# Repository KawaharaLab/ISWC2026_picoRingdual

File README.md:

# picoRing *dual*

This repository contains the hardware design files, firmware, and evaluation applications for the dual-wearable system (Finger Ring and Wristband) presented in our ISWC 2026 paper.

---

## Repository Structure

The project consists of four main modules:

### 1. BLE (`/BLE`)
Contains the firmware used for baseline evaluation.
* **`ring_demo/` / `receiver_demo/`**: Firmware implemented to benchmark power consumption when the ring and wristband communicate via Bluetooth Low Energy (BLE) instead of NFC.

### 2. Circuit (`/Circuit`)
Contains the hardware design files created with KiCad (v7 or later).
* **`ring/`**: Schematic and PCB layout files for the finger-worn ring node.
* **`wristband/`**: Schematic and PCB layout files for the wristband module.

### 3. Firmware (`/Firmware`)
Contains the source code for the proposed NFC-coupled system.
* **`ring/`**: STM32CubeIDE project for the STM32U375KGUx MCU embedded in the ring, including drivers for the `ICM45605` IMU and `ST25DVxxKC` NFC tag.
* **`wristband/`**: PlatformIO project for the Seeed Studio XIAO based wristband, utilizing the ST `NFC-RFAL` library for NFC polling.

### 4. GUI (`/GUI`)
Contains the following applications for system demonstration and data visualization:
* **`sensor_viewer/`**: Displays raw data from the trackball and IMU quaternion outputs.
* **`3d_viewer/`**: Visualizes data from both hands' trackballs and IMU sensors to dynamically control 3D models of the ring and trackball icons.
* **`map/`**: A web-based application that displays routes selected from a menu. Supports map scrolling and zooming via the trackball (Requires a Google Maps API key).
* **`game/`**: A 3D application with two selectable modes via a menu:
  * **Video Mode**: Supports playback, pausing, and skipping of videos.
  * **Game Mode**: Enables aiming and reloading with the right hand, and locomotion with the left hand.
* **`email/`**: Supports email selection and message body scrolling.
* **`cooking/`**: Detects hand movements via the IMU and triggers a warning alert if the hand stops moving for a specific duration.

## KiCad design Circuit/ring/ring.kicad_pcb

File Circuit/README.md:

# Hardware Circuit Design

This directory contains the hardware design and PCB layout files for the *picoRing dual* system. 

## Directory Structure

* **`ring/`**: Schematic and PCB design files for the  ring.
* **`wristband/`**: Schematic and PCB design files for the wristband.

---

## Design Environment

* **Software**: **KiCad (v7.0 or later)**
* **Project Files**: `.kicad_pro`

To inspect or modify the designs, open the respective `.kicad_pro` file inside the `ring/` or `wristband/` directory using KiCad.

---

## Important Notice for Replication

* **Component Footprints & Libraries**: Custom or third-party footprint/symbol libraries used in these designs are not bundled in this repository. Users must set up, map, or substitute their own component libraries and footprints according to their local KiCad environment and parts availability.

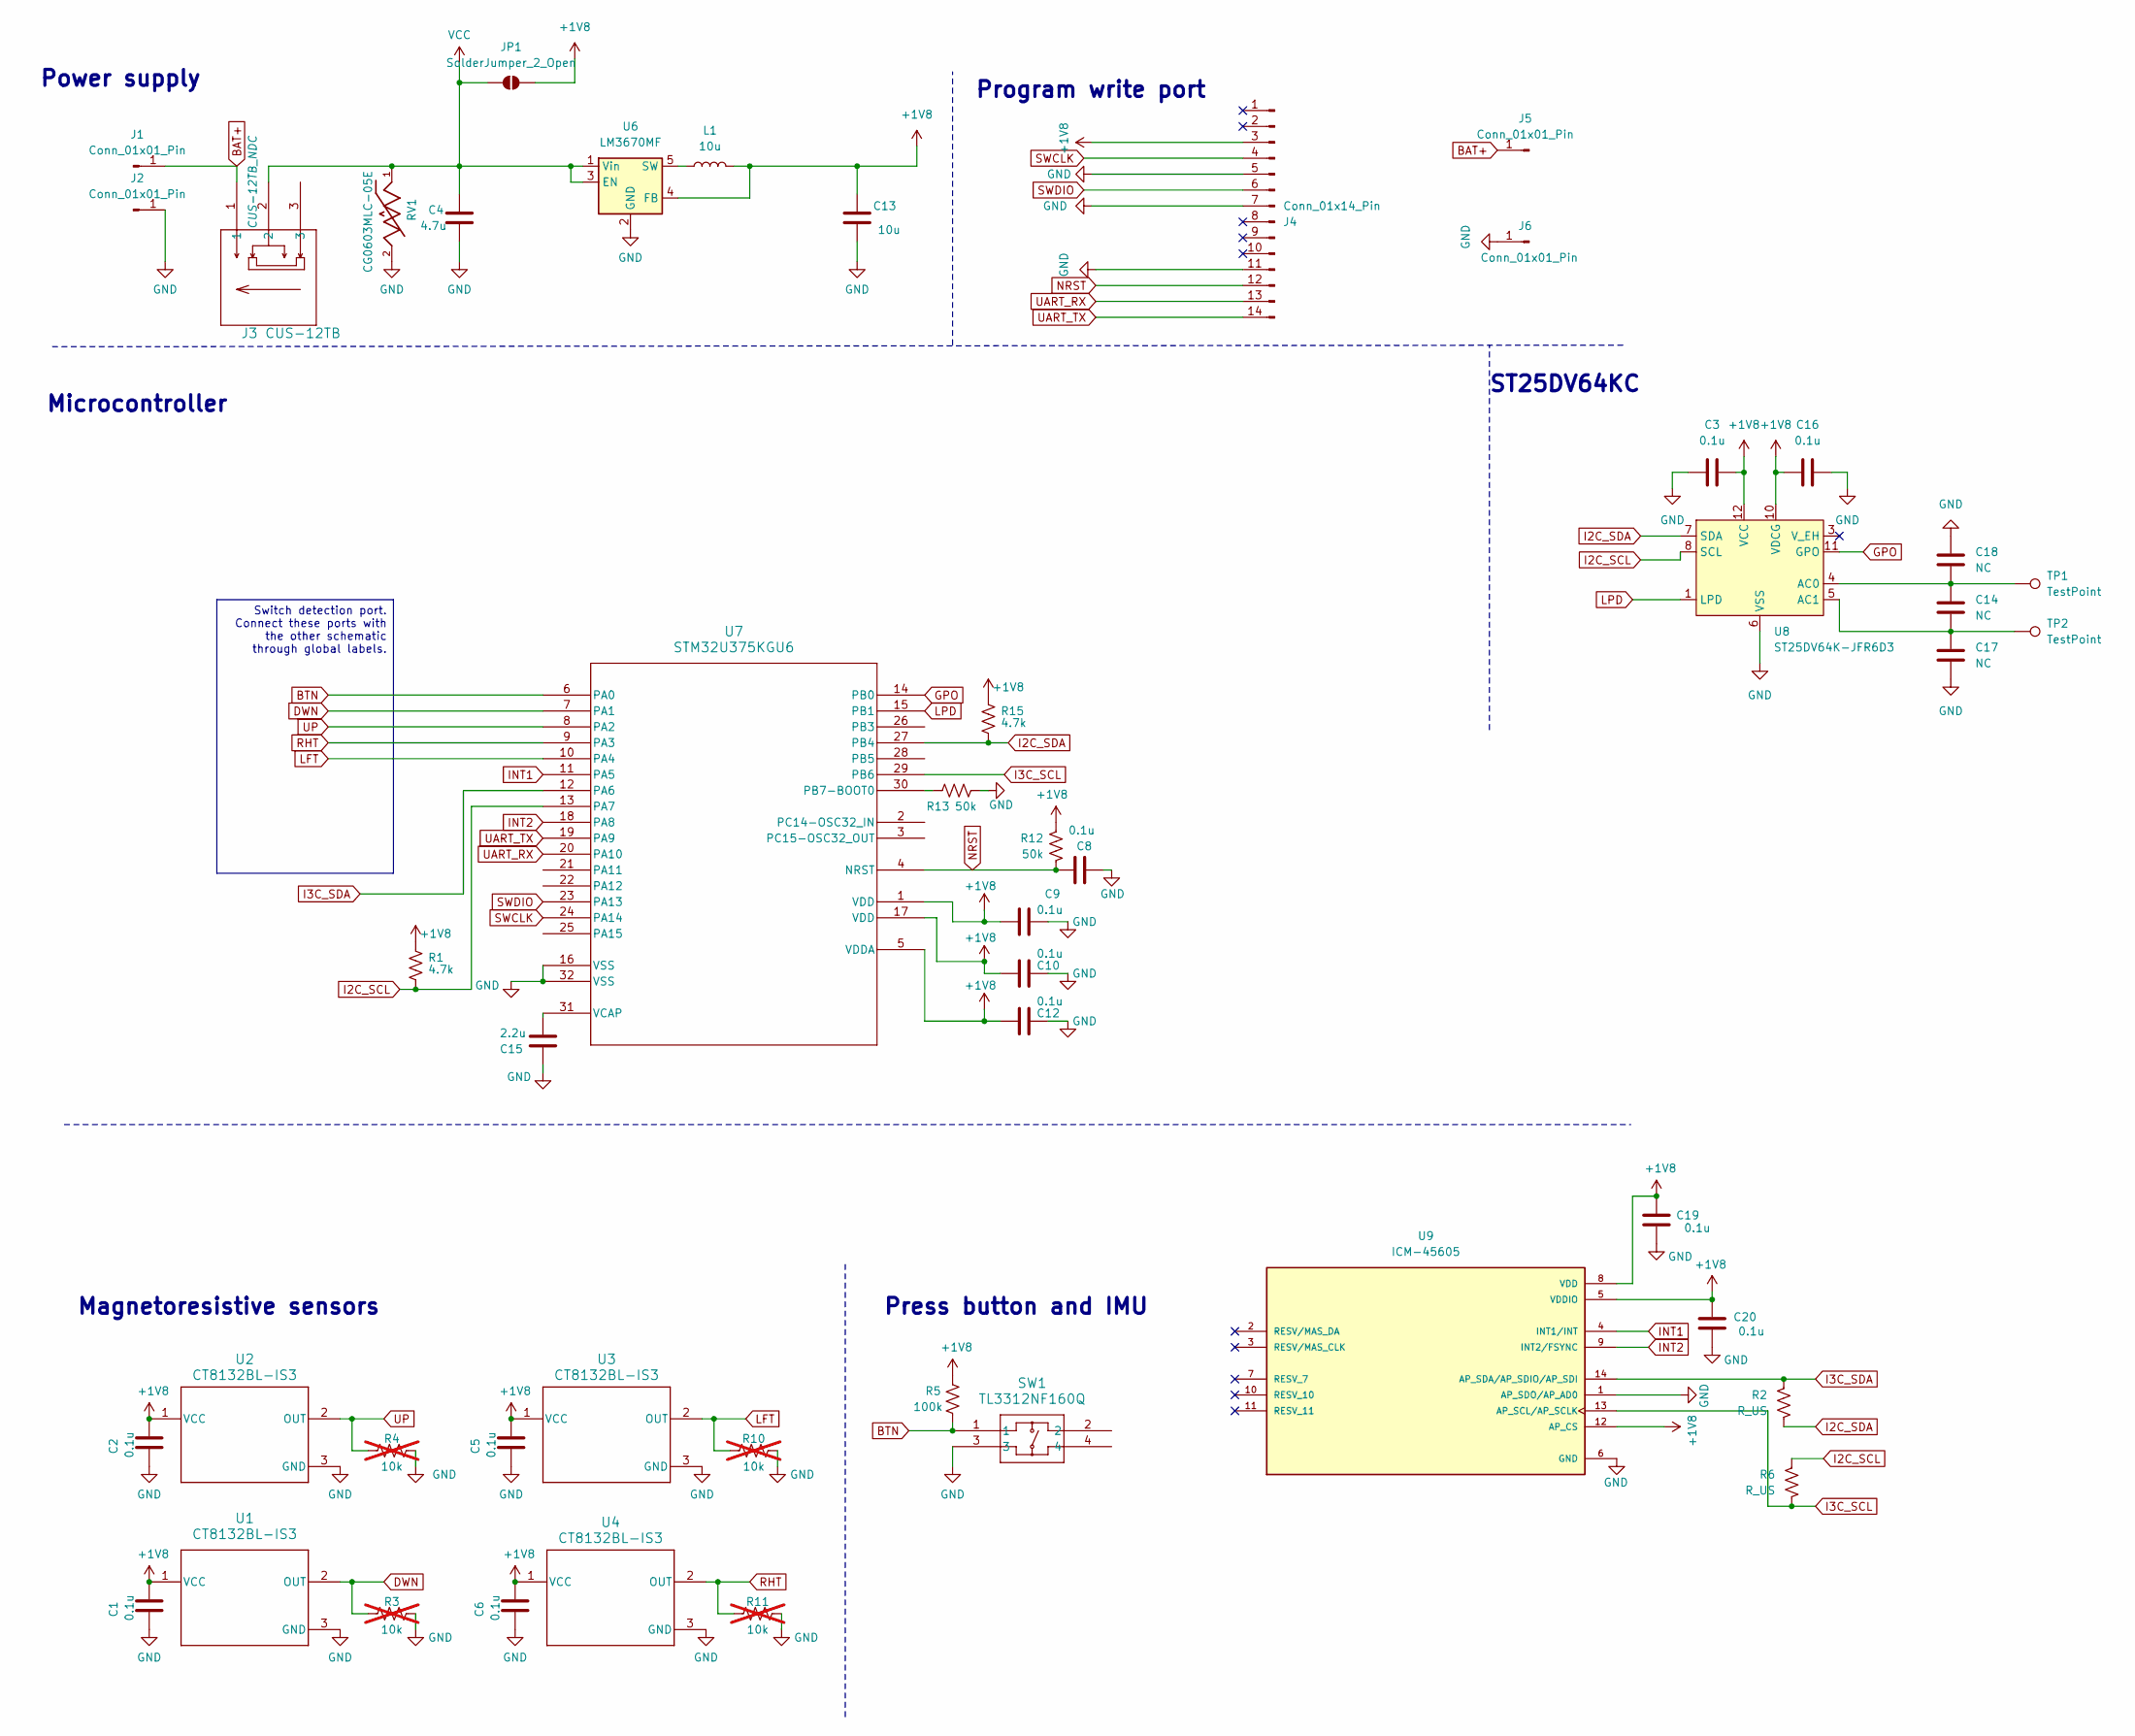
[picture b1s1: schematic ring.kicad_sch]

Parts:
C1, C2, C3, C5, C6, C8, C9, C10, C12, C16, C19, C20: 0.1u; C_0402_1005Metric
C4: 4.7u; C_0402_1005Metric
C13: 10u; C_0402_1005Metric
C14, C17, C18: NC; C_0402_1005Metric_Pad0.74x0.62mm_HandSolder
C15: 2.2u; C_0402_1005Metric
J1, J2, J5, J6: Conn_01x01_Pin; padFront
J3: CUS-12TB; CUS-12TB_NDC
J4: Conn_01x14_Pin; Tag-Connect_TC2070-IDC-FP_2x07_P1.27mm_Vertical
JP1: SolderJumper_2_Open; SolderJumper-2_P1.3mm_Open_RoundedPad1.0x1.5mm
L1: 10u; L_0805_2012Metric
R1, R15: 4.7k; R_0402_1005Metric
R2, R6: R_US; R_0402_1005Metric_Pad0.72x0.64mm_HandSolder
R3, R4, R10, R11: 10k; R_0402_1005Metric; not fitted
R5: 100k; R_0402_1005Metric
R12, R13: 50k; R_0402_1005Metric
RV1: CG0603MLC-05E; VARC1608X56N; PARTREV E
SW1: TL3312NF160Q; TL3312NF160Q_EWI
TP1, TP2: TestPoint; PinHeader_1x01_P1.27mm_Vertical
U1, U2, U3, U4: CT8132BL-IS3; DBZ0003A-IPC_C
U6: LM3670MF; TSOT-23-5
U7: STM32U375KGU6; UFQFPN-32_STM
U8: ST25DV64K-JFR6D3; ST_UFDFPN-12-1EP_3x3mm_P0.5mm_EP1.4x2.55mm
U9: ICM-45605; XDCR_ICM-45605; PARTREV 1.0

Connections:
+1V8: C1.2, C2.2, C3.2, C5.2, C6.2, C9.1, C10.1, C12.1, C13.1, C16.1, C19.2, C20.2, J4.3, JP1.2 (B), L1.2, R1.2, R5.2, R12.2, R15.2, U1.1 (VCC), U2.1 (VCC), U3.1 (VCC), U4.1 (VCC), U6.4 (FB), U7.1 (VDD), U7.5 (VDDA), U7.17 (VDD), U8.10 (VDCG), U8.12 (VCC), U9.5 (VDDIO), U9.8 (VDD), U9.12 (AP_CS); also elsewhere on the board
BAT+: J1.1, J3.1, J5.1; also elsewhere on the board
BTN: R5.1, SW1.1, U7.6 (PA0)
DWN: R3.1, U1.2 (OUT), U7.7 (PA1)
GND: C1.1, C2.1, C3.1, C4.1, C5.1, C6.1, C8.2, C9.2, C10.2, C12.2, C13.2, C15.1, C16.2, C17.2, C18.1, C19.1, C20.1, J2.1, J4.5, J4.7, J4.11, J6.1, R3.2, R4.2, R10.2, R11.2, R13.1, RV1.2, SW1.3, U1.3 (GND), U2.3 (GND), U3.3 (GND), U4.3 (GND), U6.2 (GND), U7.16 (VSS), U7.32 (VSS), U8.6 (VSS), U9.1 (AP_SDO/AP_AD0), U9.6 (GND); also elsewhere on the board
GPO: U7.14 (PB0), U8.11 (GPO)
I2C_SCL: R1.1, R6.1, U7.13 (PA7), U8.8 (SCL)
I2C_SDA: R2.2, R15.1, U7.27 (PB4), U8.7 (SDA)
I3C_SCL: R6.2, U7.29 (PB6), U9.13 (AP_SCL/AP_SCLK); also elsewhere on the board
I3C_SDA: R2.1, U7.12 (PA6), U9.14 (AP_SDA/AP_SDIO/AP_SDI)
INT1: U7.11 (PA5), U9.4 (INT1/INT)
INT2: U7.18 (PA8), U9.9 (INT2/FSYNC)
LFT: R10.1, U3.2 (OUT), U7.10 (PA4)
LPD: U7.15 (PB1), U8.1 (LPD)
NRST: C8.1, J4.12, R12.1, U7.4 (NRST)
unnamed: L1.1, U6.5 (SW)
unnamed: R13.2, U7.30 (PB7-BOOT0)
unnamed: C15.2, U7.31 (VCAP)
unnamed: C14.1, C18.2, TP1.1, U8.4 (AC0)
unnamed: C14.2, C17.1, TP2.1, U8.5 (AC1)
RHT: R11.1, U4.2 (OUT), U7.9 (PA3)
SWCLK: J4.4, U7.24 (PA14)
SWDIO: J4.6, U7.23 (PA13)
UART_RX: J4.13, U7.20 (PA10)
UART_TX: J4.14, U7.19 (PA9)
UP: R4.1, U2.2 (OUT), U7.8 (PA2)
VCC: C4.2, J3.2, JP1.1 (A), RV1.1, U6.1 (Vin), U6.3 (EN)

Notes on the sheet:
Program write port
Press button and IMU
Microcontroller
Magnetoresistive sensors
ST25DV64KC
Power supply
Switch detection port. Connect these ports with the other schematic through global labels.

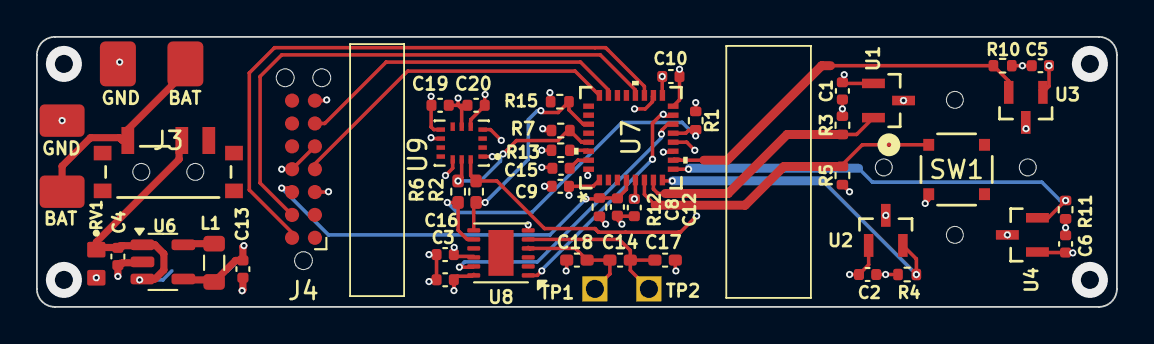
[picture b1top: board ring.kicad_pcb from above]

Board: 4 copper layers, 60.0 x 15.0 mm, 50 parts (1 on the bottom side), 27 nets.

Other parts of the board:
BAT: Conn_01x01_Pin; padFront
GND: Conn_01x01_Pin; padFront
R7: 0; R_0402_1005Metric

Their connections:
+1V8: R7.1; also elsewhere on the board
BAT+: BAT.1; also elsewhere on the board
GND: GND.1; also elsewhere on the board
I3C_SCL: R7.2; also elsewhere on the board

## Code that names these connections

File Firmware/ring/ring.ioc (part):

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Mcu.Name=STM32U375KGUx
Mcu.Package=UQFN32
Mcu.UserName=STM32U375KGUx
PA0.GPIOParameters=GPIO_Label
PA0.GPIO_Label=BTN
PA0.Signal=GPIO_Input
PA1.GPIOParameters=GPIO_Label
PA1.GPIO_Label=DWN
PA1.Signal=GPIO_Input
PA10.Mode=Asynchronous
PA10.Signal=USART1_RX
PA2.GPIOParameters=GPIO_Label
PA2.GPIO_Label=UP
PA2.Signal=GPIO_Input
PA3.GPIOParameters=GPIO_Label
PA3.GPIO_Label=RHT
PA3.Signal=GPIO_Input
PA4.GPIOParameters=GPIO_Label
PA4.GPIO_Label=LFT
PA4.Signal=GPIO_Input
PA5.GPIOParameters=GPIO_Label
PA5.GPIO_Label=INT1
PA5.Signal=GPXTI5
PA7.Mode=I2C
PA7.Signal=I2C3_SCL
PA8.GPIOParameters=GPIO_Label
PA8.GPIO_Label=INT2
PA8.Signal=GPXTI8
PA9.Mode=Asynchronous
PA9.Signal=USART1_TX
PB0.GPIOParameters=GPIO_Label
PB0.GPIO_Label=GPO
PB0.Signal=GPXTI0
PB1.GPIOParameters=GPIO_Label
PB1.GPIO_Label=LPD
PB1.Signal=GPIO_Output
PB4\ (NJTRST).Mode=I2C
PB4\ (NJTRST).Signal=I2C3_SDA
RCC.HSE_VALUE=16000000
RCC.SYSCLKFreq_VALUE=3000000
board=custom

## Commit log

2026-05-30 Initial commit with project source code and directory-level READMEs
2026-06-02 Update BLE comments
